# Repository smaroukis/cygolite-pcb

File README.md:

PCB (KiCad files + libraries) of a Cygolite bike light (white LED). Constant current driver [MIC4802YME](https://www.digikey.jp/ja/products/detail/microchip-technology/MIC4802YME/2621444) set at 750mA with Li-Ion battery connector and [MCP73831](https://www.digikey.jp/en/products/detail/microchip-technology/MCP73831T-2ACI-OT/964301) Li-Ion charger. ATTiny202 used for PWM output, status LED control and button sensing. USB-C 6P (power only) connector for charging. UART and UDPI pin headers. 

Using 0603 resistor and capacitors for best solderability + size combo.

Demonstration of circuits for multiplexing PWM<>Analog Input and Button Sense <> LED driver.

TODO add photo of the light itself

## Schematic and Images
See the [Schematic](Schematic.pdf) in `/Schematic.pdf`

PCB - top

PCB - 3D top

PCB - 3D back (shows USB)

Close up of battery connector

## BOM

See [BOM.csv][BOM.csv]

| Reference | Qty | Value             | MPN               | Manufacturer                        | Description                                                                                                |
|-----------|-----|-------------------|-------------------|-------------------------------------|------------------------------------------------------------------------------------------------------------|
| C1,C2     | 2   | 4.7u              | (Generic)         | (Generic)                           | Unpolarized capacitor                                                                                      |
| D1        | 1   | SMAJ5.0CA         | SMAJ5.0CA         | Littelfuse                          | TVS DIODE 5VWM 9.2VC DO214AC                                                                               |
| J1        | 1   | USB4125-GF-A-0190 | USB4125-GF-A-0190 | GCT                                 | USB Power-Only 6P Type-C Receptacle connector                                                              |
| J2        | 1   | 530480310         | 530480310         | Molex                               | CONN HEADER R/A 3POS 1.25MM                                                                                |
| J3        | 1   | Conn_01x03_Socket | N/A               | (Generic)                           | Generic connector, single row, 01x03, script generated                                                     |
| J4        | 1   | Conn_01x02_Socket | N/A               | (Generic)                           | Generic connector, single row, 01x02, script generated                                                     |
| LED1      | 1   | APHBM2012SURKCGKC | APHBM2012SURKCGKC | Kingbright                          | LED GREEN/RED CLEAR 2012(mm) SMD                                                                           |
| R1,R2     | 2   | 5.1K              | (Generic)         | (Generic)                           | Resistor 0603 5.1K                                                                                         |
| R3,R12    | 2   | 0                 | (Generic)         | (Generic)                           | Resistor 0603 0Ohm                                                                                         |
| R4,R5,R8  | 3   | 2K                | (Generic)         | (Generic)                           | Resistor 0603 2KOhm                                                                                        |
| R6        | 1   | 1M                | (Generic)         | (Generic)                           | Resistor                                                                                                   |
| R7,R9,R10 | 3   | 10K               | (Generic)         | (Generic)                           | Resistor 0603 10KOhm                                                                                       |
| R11       | 1   | 6.8K              | (Generic)         | (Generic)                           | Resistor 0603 6.8K 1%                                                                                      |
| SW1       | 1   | SW_Push           | FSM1LPTR          | TE Connectivity ALCOSWITCH Switches | Generic push-button switch, two contact pins and shield pin(s)                                             |
| U1        | 1   | ATtiny202-SS      | ATTINY202-SSN-ND  | Microchip Technology                | 20MHz, 2kB Flash, 128B SRAM, 64B EEPROM, SOIC-8                                                            |
| U2        | 1   | MCP73831-2-OT     | MCP73831T-2ACI/OT | Microchip Technology                | Single cell, Li-Ion/Li-Po charge management controller, 4.20V, Tri-State Status Output, in SOT23-5 package |
| U3        | 1   | MIC4802YME        | MIC4802YME        | Microchip Technology                | LED Driver IC 1 Output Linear PWM Dimming 800mA 8-SOIC-EP                                                  |

## TODOs
- [ ] add schematic pdfs and board image
- [ ] add multiplexing superposition explanation

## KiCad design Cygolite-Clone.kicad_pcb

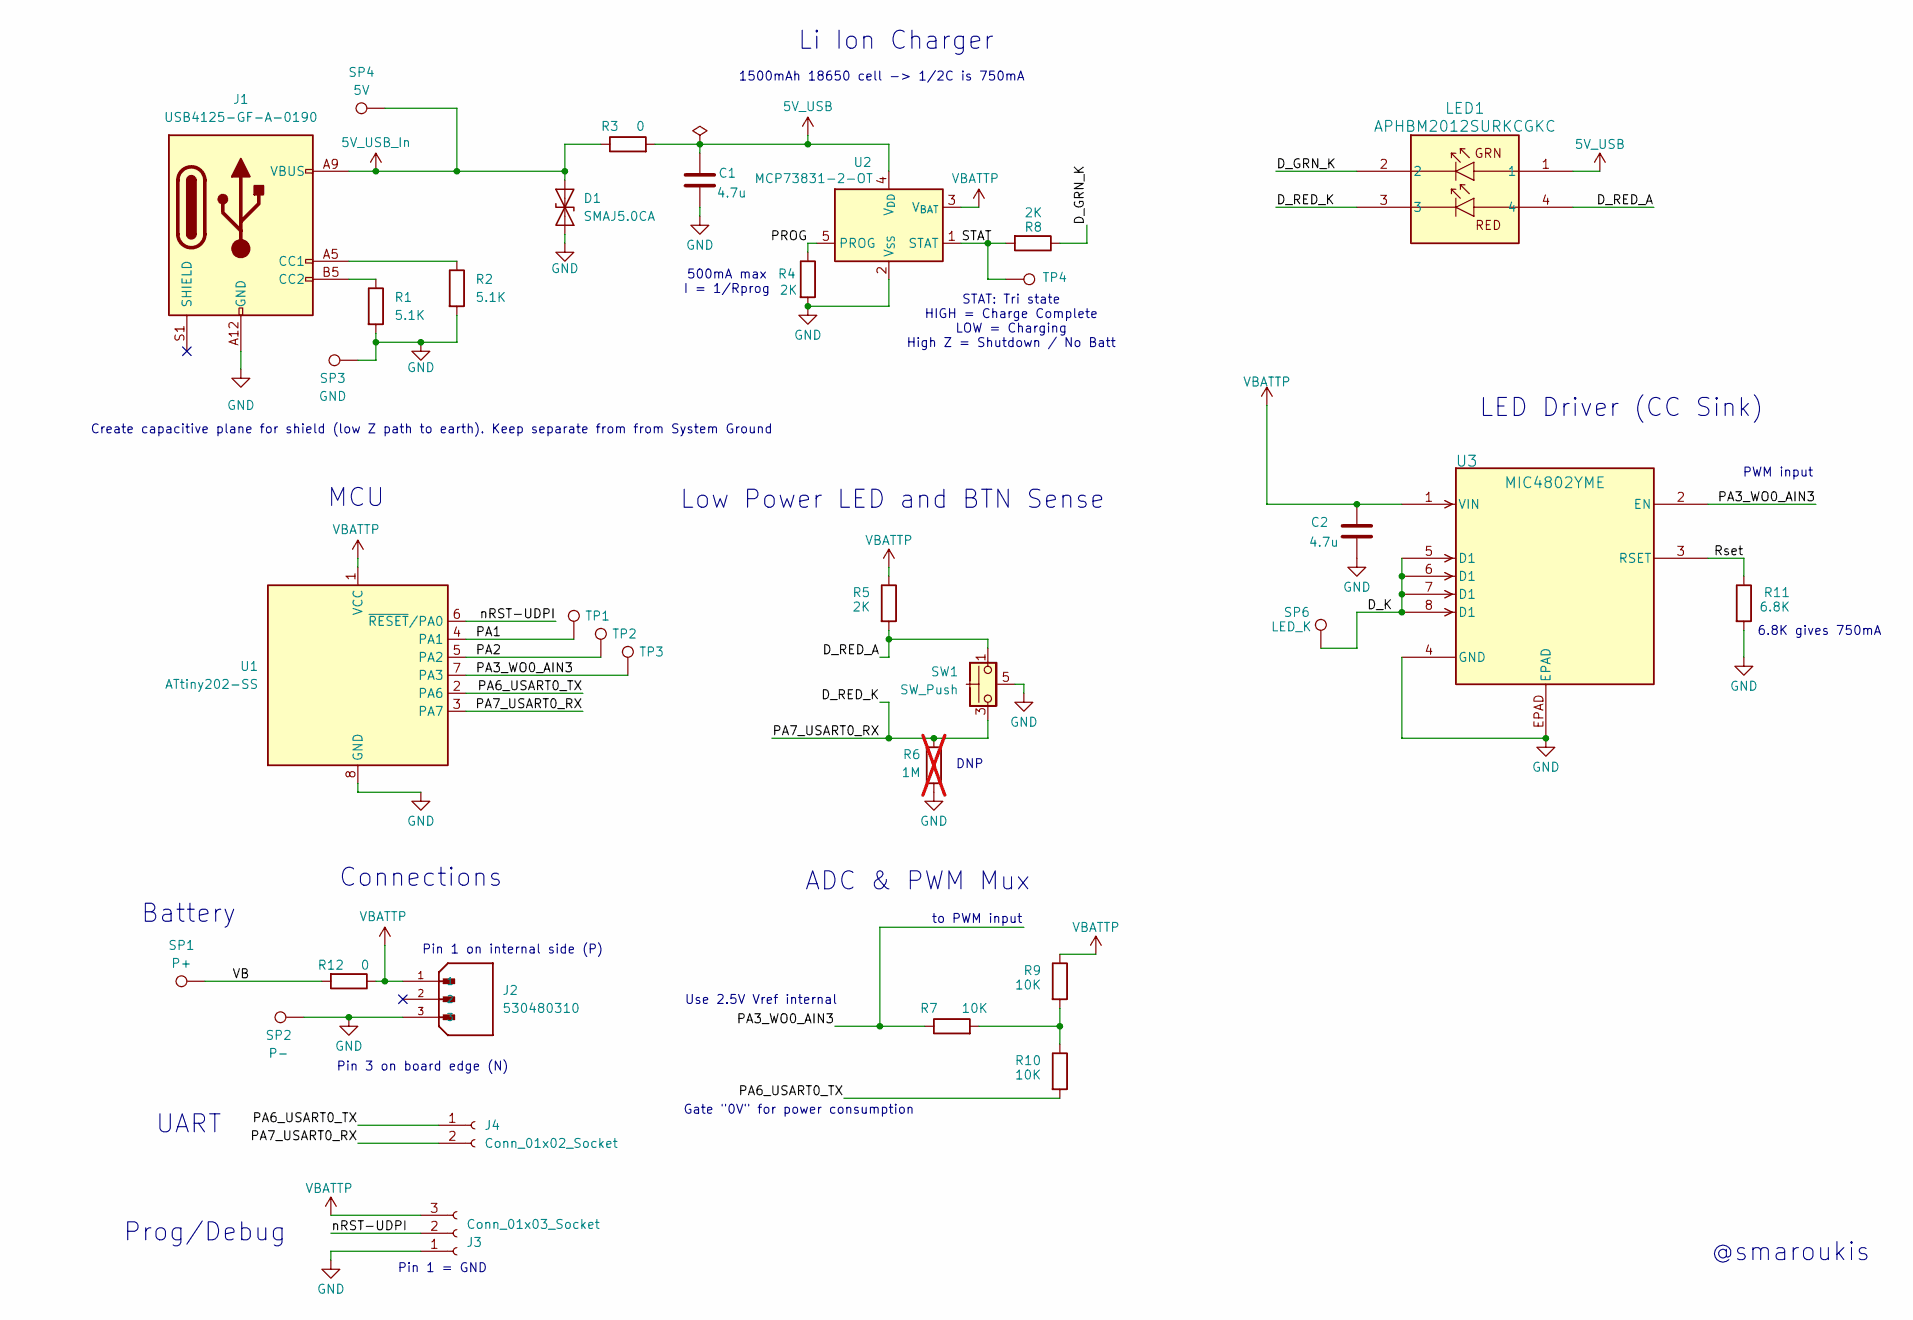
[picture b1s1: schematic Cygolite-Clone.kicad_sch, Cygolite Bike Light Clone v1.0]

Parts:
C1, C2: 4.7u; C_0603_1608Metric_Pad1.08x0.95mm_HandSolder; MPN (Generic)
D1: SMAJ5.0CA; D_SMA; MPN SMAJ5.0CA
J1: USB4125-GF-A-0190; CONN6_125-GF-A-0190_GCT; MPN USB4125-GF-A-0190
J2: 530480310; MOLEX_530480310; PARTREV A
J3: Conn_01x03_Socket; PinHeader_1x03_P2.54mm_Vertical; MPN N/A
J4: Conn_01x02_Socket; PinHeader_1x02_P2.54mm_Vertical; MPN N/A
LED1: APHBM2012SURKCGKC; APHBM2012_KNB; MPN APHBM2012SURKCGKC
R1, R2: 5.1K; R_0603_1608Metric_Pad0.98x0.95mm_HandSolder; MPN (Generic)
R3, R12: 0; R_0603_1608Metric_Pad0.98x0.95mm_HandSolder; MPN (Generic)
R4, R5, R8: 2K; R_0603_1608Metric_Pad0.98x0.95mm_HandSolder; MPN (Generic)
R6: 1M; R_0603_1608Metric_Pad0.98x0.95mm_HandSolder; MPN (Generic); not fitted
R7, R9, R10: 10K; R_0603_1608Metric_Pad0.98x0.95mm_HandSolder; MPN (Generic)
R11: 6.8K; R_0603_1608Metric_Pad0.98x0.95mm_HandSolder; MPN (Generic)
SP1: P+; SolderWirePad_1x01_SMD_1x2mm; MPN N/A
SP2: P-; SolderWirePad_1x01_SMD_1x2mm; MPN N/A
SP3: GND; SolderWirePad_1x01_SMD_1x2mm; MPN N/A
SP4: 5V; SolderWirePad_1x01_SMD_1x2mm; MPN N/A
SP6: LED_K; SolderWirePad_1x01_SMD_1x2mm; MPN N/A
SW1: SW_Push; SWITCH_FSM1LPA_TYC; MPN FSM1LPTR
TP1, TP2, TP3: U2_VDD; TestPoint_Pad_D1.0mm; MPN N/A
TP4: STAT; TestPoint_Pad_D1.0mm; MPN N/A
U1: ATtiny202-SS; SOIC-8_3.9x4.9mm_P1.27mm; MPN ATTINY202-SSN-ND
U2: MCP73831-2-OT; SOT-23-5; MPN MCP73831T-2ACI/OT
U3: MIC4802YME; SOIC-8_ME_MCL; MPN MIC4802YME

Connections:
5V_USB: C1.1, LED1.1, R3.2, U2.4 (V_{DD})
5V_USB_In: D1.2 (A2), J1.A9 (VBUS), J1.B9 (VBUS), R3.1, SP4.1
/D_GRN_K: LED1.2, R8.1
/D_K: SP6.1, U3.5 (D1), U3.6 (D1), U3.7 (D1), U3.8 (D1)
/D_RED_A: LED1.4, R5.2, SW1.1, SW1.2
/D_RED_K: J4.2, LED1.3, R6.1, SW1.3, SW1.4, U1.3 (PA7)
/PA1: TP1.1, U1.4 (PA1)
/PA2: TP2.1, U1.5 (PA2)
/PA3_WO0_AIN3: R7.1, TP3.1, U1.7 (PA3), U3.2 (EN)
/PA6_USART0_TX: J4.1, R10.2, U1.2 (PA6)
/PROG: R4.1, U2.5 (PROG)
/Rset: R11.1, U3.3 (RSET)
/STAT: R8.2, TP4.1, U2.1 (STAT)
/VB: R12.2, SP1.1
/nRST-UDPI: J3.2, U1.6 (~RESET/PA0)
GND: C1.2, C2.2, D1.1 (A1), J1.A12 (GND), J1.B12 (GND), J2.3, J3.1, R1.2, R2.2, R4.2, R6.2, R11.2, SP2.1, SP3.1, SW1.5 (SHD), U1.8 (GND), U2.2 (V_{SS}), U3.4 (GND), U3.EPAD
unnamed: J1.A5 (CC1), R2.1
unnamed: J1.B5 (CC2), R1.1
unnamed: R7.2, R9.2, R10.1
VBATTP: C2.1, J2.1, J3.3, R5.1, R9.1, R12.1, U1.1 (VCC), U2.3 (V_{BAT}), U3.1 (VIN)

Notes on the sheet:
500mA max I = 1/Rprog
STAT: Tri state HIGH = Charge Complete LOW = Charging High Z = Shutdown / No Batt
Use 2.5V Vref internal
Li Ion Charger
6.8K gives 750mA
Pin 1 on internal side (P)
Low Power LED and BTN Sense
Prog/Debug
MCU
LED Driver (CC Sink)
ADC & PWM Mux
Pin 3 on board edge (N)
Gate "0V" for power consumption
Connections
Create capacitive plane for shield (low Z path to earth). Keep separate from from System Ground
to PWM input
DNP
Pin 1 = GND
Battery
1500mAh 18650 cell -> 1/2C is 750mA
PWM input
@smaroukis
UART

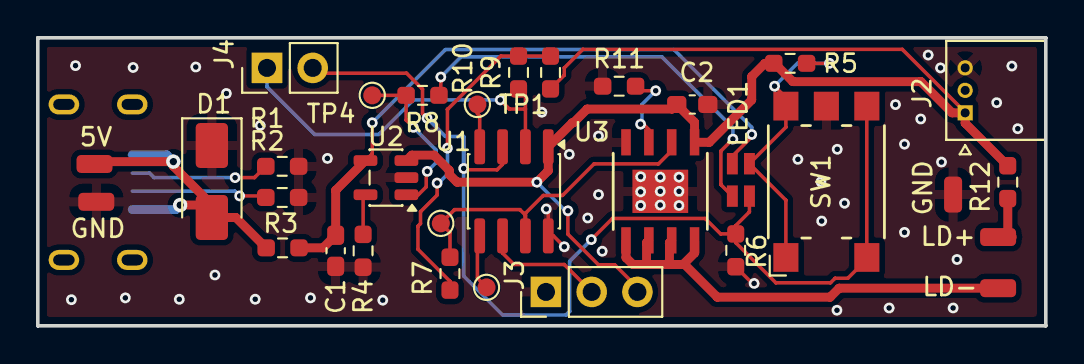
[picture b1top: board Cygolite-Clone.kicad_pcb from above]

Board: 2 copper layers, 56.0 x 16.0 mm, 33 parts (1 on the bottom side), 20 nets.

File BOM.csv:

Reference,Qty,Value,MPN,Manufacturer,Description,Footprint,Supplier 1,Supplier 1 URL
"C1,C2",2,4.7u,(Generic),(Generic),Unpolarized capacitor,Capacitor_SMD:C_0603_1608Metric_Pad1.08x0.95mm_HandSolder,(Generic),
D1,1,SMAJ5.0CA,SMAJ5.0CA,Littelfuse,TVS DIODE 5VWM 9.2VC DO214AC,Diode_SMD:D_SMA,Digikey,https://www.digikey.jp/en/products/detail/littelfuse-inc/SMA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
J1,1,USB4125-GF-A-0190,USB4125-GF-A-0190,GCT,USB Power-Only 6P Type-C Receptacle connector,a_project_footprints:CONN6_125-GF-A-0190_GCT,Digikey,https://www.digikey.jp/en/products/detail/gct/USB4125-GF-A-0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
J2,1,530480310,530480310,Molex,CONN HEADER R/A 3POS 1.25MM,a_project_footprints:MOLEX_530480310,Digikey,https://www.digikey.jp/en/products/detail/molex/0530480310/2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
J3,1,Conn_01x03_Socket,N/A,(Generic),"Generic connector, single row, 01x03, script generated",Connector_PinHeader_2.54mm:PinHeader_1x03_P2.54mm_Vertical,(Generic),
J4,1,Conn_01x02_Socket,N/A,(Generic),"Generic connector, single row, 01x02, script generated",Connector_PinHeader_2.54mm:PinHeader_1x02_P2.54mm_Vertical,(Generic),
LED1,1,APHBM2012SURKCGKC,APHBM2012SURKCGKC,Kingbright,LED GREEN/RED CLEAR 2012(mm) SMD,a_project_footprints:APHBM2012_KNB,Digikey,https://www.digikey.jp/ja/products/detail/kingbright/APHBM20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
"R1,R2",2,5.1K,(Generic),(Generic),Resistor 0603 5.1K,Resistor_SMD:R_0603_1608Metric_Pad0.98x0.95mm_HandSolder,(Generic),
"R3,R12",2,0,(Generic),(Generic),Resistor 0603 0Ohm,Resistor_SMD:R_0603_1608Metric_Pad0.98x0.95mm_HandSolder,(Generic),
"R4,R5,R8",3,2K,(Generic),(Generic),Resistor 0603 2KOhm,Resistor_SMD:R_0603_1608Metric_Pad0.98x0.95mm_HandSolder,(Generic),
R6,1,1M,(Generic),(Generic),Resistor,Resistor_SMD:R_0603_1608Metric_Pad0.98x0.95mm_HandSolder,(Generic),
"R7,R9,R10",3,10K,(Generic),(Generic),Resistor 0603 10KOhm,Resistor_SMD:R_0603_1608Metric_Pad0.98x0.95mm_HandSolder,(Generic),
R11,1,6.8K,(Generic),(Generic),Resistor 0603 6.8K 1%,Resistor_SMD:R_0603_1608Metric_Pad0.98x0.95mm_HandSolder,(Generic),
SW1,1,SW_Push,FSM1LPTR,TE Connectivity ALCOSWITCH Switches,"Generic push-button switch, two contact pins and shield pin(s)",a_project_footprints:SWITCH_FSM1LPA_TYC,Digikey,https://www.digikey.jp/en/products/detail/te-connectivity-al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
U1,1,ATtiny202-SS,ATTINY202-SSN-ND,Microchip Technology,"20MHz, 2kB Flash, 128B SRAM, 64B EEPROM, SOIC-8",Package_SO:SOIC-8_3.9x4.9mm_P1.27mm,Digikey,https://www.digikey.jp/ja/products/detail/microchip-technolo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
U2,1,MCP73831-2-OT,MCP73831T-2ACI/OT,Microchip Technology,"Single cell, Li-Ion/Li-Po charge management controller, 4.20V, Tri-State Status Output, in SOT23-5 package",Package_TO_SOT_SMD:SOT-23-5,Digikey,https://www.digikey.jp/en/products/detail/microchip-technolo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
U3,1,MIC4802YME,MIC4802YME,Microchip Technology,LED Driver IC 1 Output Linear PWM Dimming 800mA 8-SOIC-EP,a_project_footprints:SOIC-8_ME_MCL,Digikey,https://www.digikey.jp/ja/products/detail/microchip-technolo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

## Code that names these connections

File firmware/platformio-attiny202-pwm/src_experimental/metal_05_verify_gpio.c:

#define F_CPU 3333333UL

#include <avr/io.h>
#include <util/delay.h>
#include <stdint.h>

// Blinks each gpio pin a pre-determined unique set of times for verification of routing.

static void blink_pin(uint8_t pin_bm, uint8_t count) {
    for (uint8_t i = 0; i < count; i++) {
        PORTA.OUTSET = pin_bm;
        _delay_ms(150);

        PORTA.OUTCLR = pin_bm;
        _delay_ms(150);
    }

    _delay_ms(100);
}

int main(void) {
    // Configure all testable GPIO pins as outputs.
    // Avoid PA0 because it is UPDI/programming.
    PORTA.DIRSET = PIN1_bm | PIN2_bm | PIN3_bm | PIN6_bm | PIN7_bm;

    while (1) {
        blink_pin(PIN1_bm, 4);  // PA1 <> Package Pin 4
        blink_pin(PIN2_bm, 5);  // PA2 <> Package Pin 5
        blink_pin(PIN3_bm, 7);  // PA3 <> Package Pin 7
        blink_pin(PIN6_bm, 2);  // PA6 <> Package Pin 2
        blink_pin(PIN7_bm, 3);  // PA7 <> Package Pin 3
    }
}

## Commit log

2026-01-03 first
2026-01-03 added Readme
2026-01-03 added backup
2026-01-12 added images, schematic, updated readme
2026-03-23 added v1.0 as built files
2026-06-15 fab outputs and pedagogical baremetal drivers
2026-06-15 example app 8 - debounce button press (active high)
2026-06-15 app 9 button input with pressed timer
2026-06-15 light controller uart print
2026-06-15 bump w changes
2026-06-16 light controller 2
